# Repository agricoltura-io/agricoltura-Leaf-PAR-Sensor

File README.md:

# agricoltura-Leaf-PAR-Sensor
A in house developed PAR sensor module

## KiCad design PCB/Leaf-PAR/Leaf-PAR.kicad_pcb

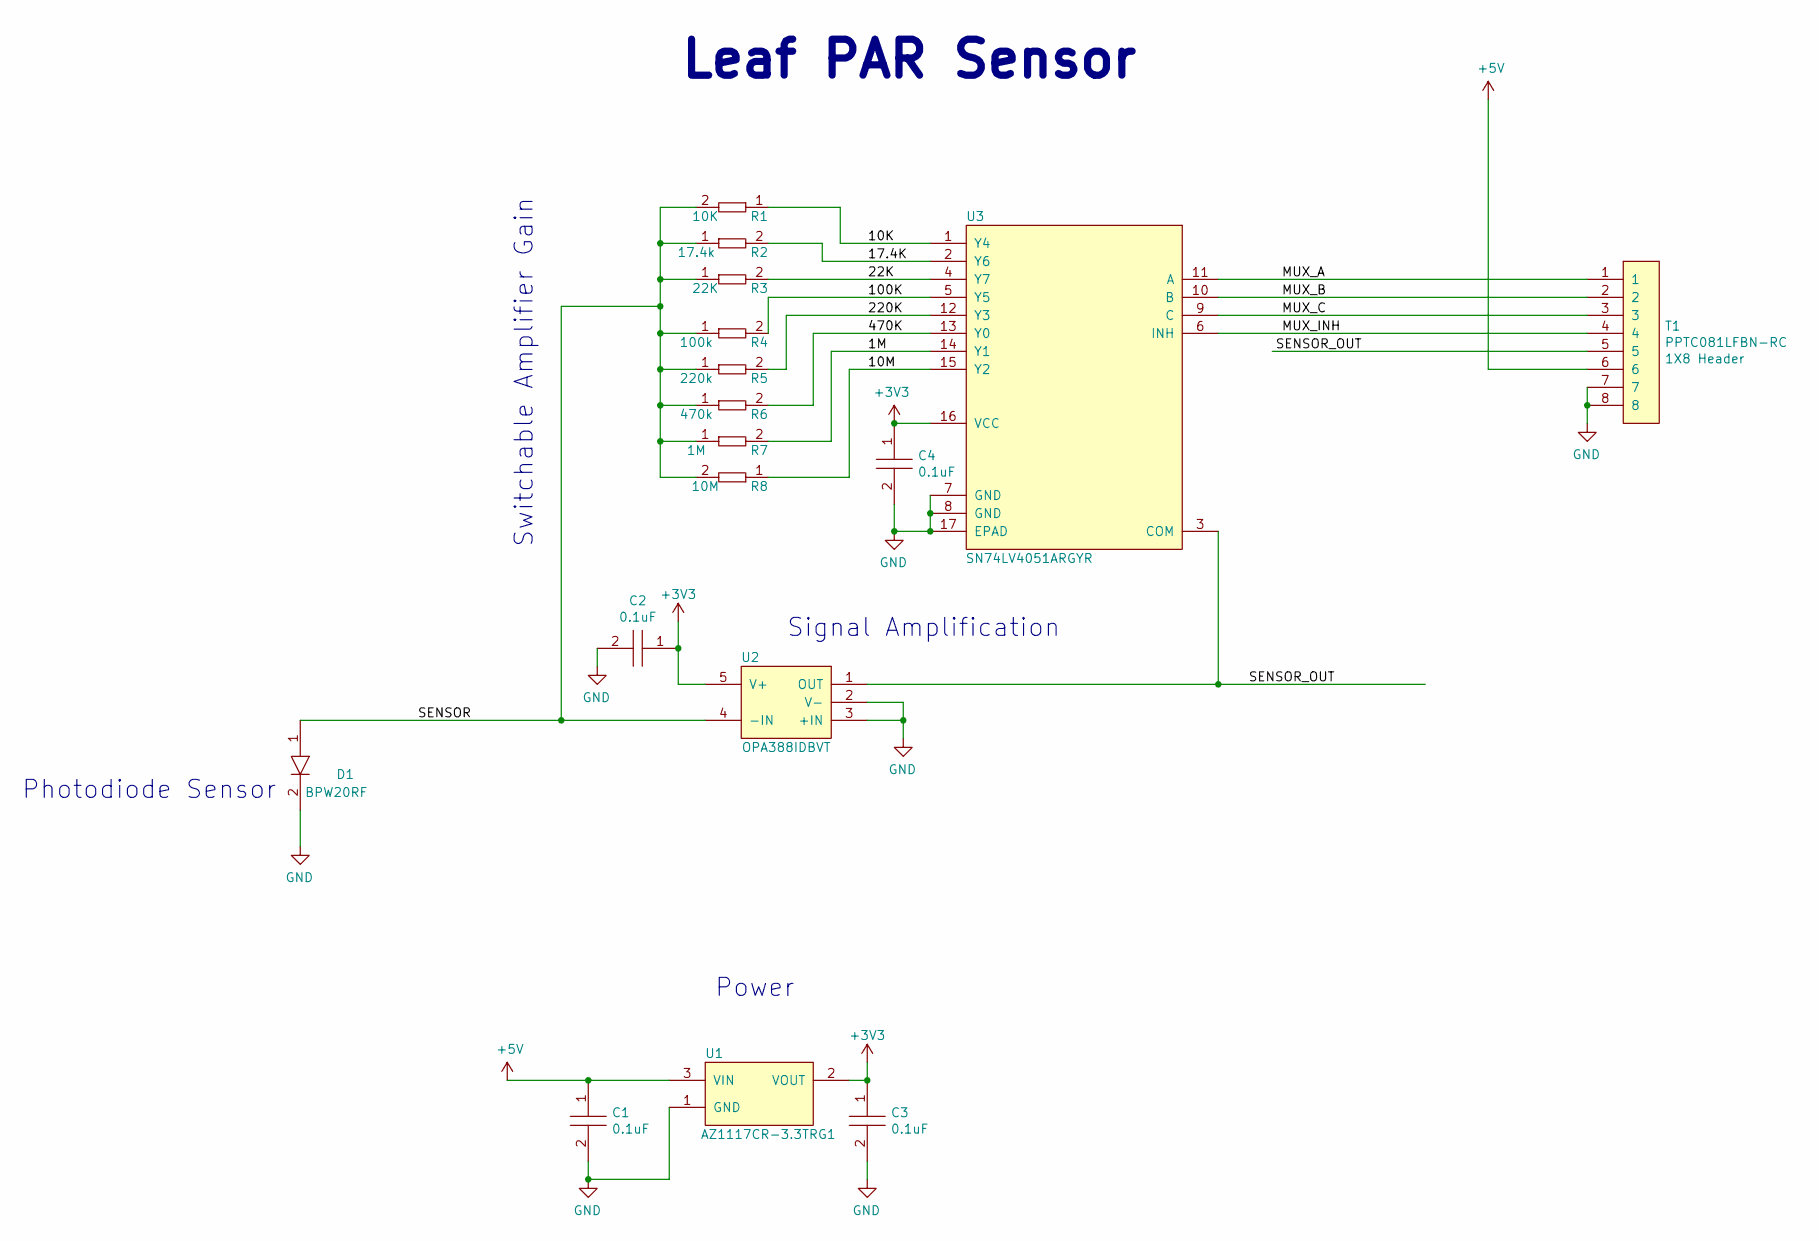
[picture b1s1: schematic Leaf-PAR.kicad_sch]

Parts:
C1: CGA3E2X7R1H104K080AA; C0603; Tolerance 10%; Voltage 50V; MFR# CGA3E2X7R1H104K080AA
C2: ECW-U1104JC9; Tolerance 5%; Voltage 100V; MFR# ECW-U1104JC9
C3, C4: C0805C104M5RACTU; C0805; Tolerance 20%; Voltage 50V; MFR# C0805C104M5RACTU
D1: BPW20RF; Tolerance *; Voltage 10V; MFR# 2.94000
R1: RC0402FR-0710KL; R0402; Tolerance 1%; Voltage *; MFR# RC0402FR-0710KL
R2: RC0402FR-0717K4L; R0402; Tolerance 1%; Voltage *; MFR# RC0402FR-0717K4L
R3: RT0402FRE0722KL; R0402; Tolerance 1%; Voltage *; MFR# RT0402FRE0722KL
R4: RC0402FR-07100KL; R0402; Tolerance 1%; Voltage *; MFR# RC0402FR-07100KL
R5: AC0402FR-07220KL; R0402; Tolerance 1%; Voltage *; MFR# AC0402FR-07220KL
R6: AC0402FR-07470KL; R0402; Tolerance 1%; Voltage *; MFR# AC0402FR-07470KL
R7: RC0402FR-071ML; R0402; Tolerance 1%; Voltage *; MFR# RC0402FR-071ML
R8: RC0402FR-0710ML; R0402; Tolerance 1%; Voltage *; MFR# RC0402FR-0710ML
T1: PPTC081LFBN-RC; Female_Header_Straight_1x08_Pitch2.54mm; Tolerance *; Voltage 250V; MFR# PPTC081LFBN-RC
U1: AZ1117CR-3.3TRG1; SOT_89; Tolerance *; Voltage 15IN, 3V3 OUT; MFR# AZ1117CR-3.3TRG1
U2: OPA388IDBVT; SOT-23-5; Tolerance *; Voltage 2.5V ~ 5.5V, ±1.25V ~ 2.75V; MFR# OPA388IDBVT
U3: SN74LV4051ARGYR; Tolerance *; Voltage 2V ~ 5.5V; MFR# SN74LV4051ARGYR

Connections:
+3V3: C2.1, C3.1, C4.1, U1.2 (VOUT), U2.5 (V+), U3.16 (VCC)
+5V: C1.1, T1.6, U1.3 (VIN)
/1M: R7.2, U3.14 (Y1)
/10K: R1.1, U3.1 (Y4)
/10M: R8.1, U3.15 (Y2)
/17.4K: R2.2, U3.2 (Y6)
/22K: R3.2, U3.4 (Y7)
/100K: R4.2, U3.5 (Y5)
/220K: R5.2, U3.12 (Y3)
/470K: R6.2, U3.13 (Y0)
/MUX_A: T1.1, U3.11 (A)
/MUX_B: T1.2, U3.10 (B)
/MUX_C: T1.3, U3.9 (C)
/MUX_INH: T1.4, U3.6 (INH)
/SENSOR: D1.1, R1.2, R2.1, R3.1, R4.1, R5.1, R6.1, R7.1, R8.2, U2.4 (-IN)
/SENSOR_OUT: T1.5, U2.1 (OUT), U3.3 (COM)
GND: C1.2, C2.2, C3.2, C4.2, D1.2, T1.7, T1.8, U1.1 (GND), U2.2 (V-), U2.3 (+IN), U3.7 (GND), U3.8 (GND), U3.17 (EPAD)

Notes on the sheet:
Leaf PAR Sensor
Signal Amplification
Power
Switchable Amplifier Gain
Photodiode Sensor

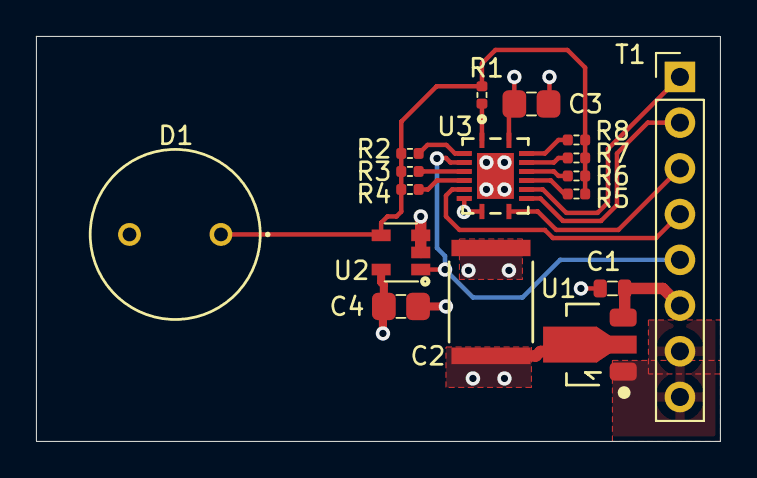
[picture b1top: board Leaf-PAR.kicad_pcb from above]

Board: 4 copper layers, 38.0 x 22.5 mm, 17 parts (0 on the bottom side), 17 nets.

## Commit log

2021-02-26 Project Created
    KiCAD Project created, main components created and added to library
2021-02-26 Schematic
    Schematic pass 1 complete, next to add interface connector, need to decide if ADC or MCU should be integrated.
2021-02-27 PCB
    PCB first pass designed, pending review before proto
2024-03-26 Create license.md
    added license
2024-03-26 KiCAD 8
    Projected updated to KiCAD 8

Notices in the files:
parts and their libraries:
Copyright 2016 Accelerated Designs. All rights reserved.
